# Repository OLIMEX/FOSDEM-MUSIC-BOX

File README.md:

# FOSDEM-MUSIC-BOX

Soldering kit programmable with Arduino IDE to play music

Product page: https://www.olimex.com/Products/Soldering-Kits/FOSDEM-MUSIC-BOX/open-source-hardware

## License
* Hardware is with CERN OHL v1.2 license
* Software is released under GPL3 License
* Documentation is released under CC BY-SA 3.0

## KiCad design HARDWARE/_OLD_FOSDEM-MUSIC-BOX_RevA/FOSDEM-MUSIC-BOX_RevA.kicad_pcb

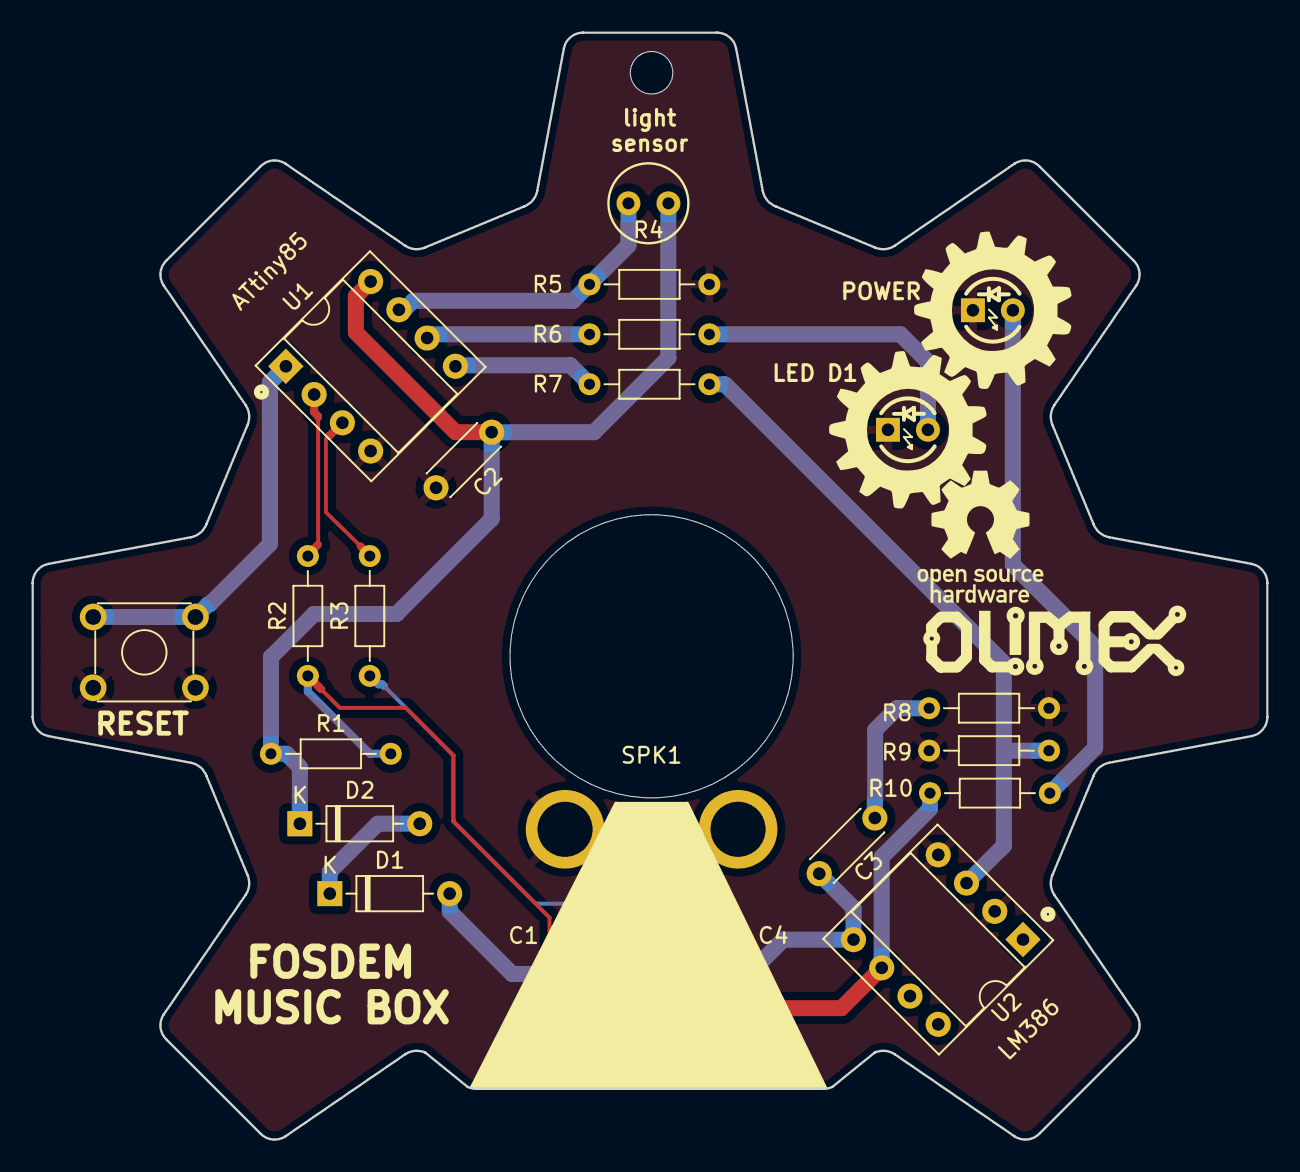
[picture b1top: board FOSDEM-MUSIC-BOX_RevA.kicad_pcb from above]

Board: 2 copper layers, 78.5 x 70.4 mm, 24 parts (0 on the bottom side), 18 nets.

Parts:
C1: 10uF; CP_Radial_D5.0mm_P2.00mm
C2: 100 nF; C_Disc_D4.3mm_W1.9mm_P5.00mm
C3: 100nF; C_Disc_D4.3mm_W1.9mm_P5.00mm
C4: 220uF_16V; CP_Radial_D6.3mm_P2.50mm
D1, D2: 1N4148; D_DO-35_SOD27_P7.62mm_Horizontal
LED1, LED2: LED_AK; LED-3mm-PTH-KA
MountingHole: NPTH_2.7mm
R1, R6, R7, R10: 1.5K; R_Axial_DIN0204_L3.6mm_D1.6mm_P7.62mm_Horizontal
R2, R3, R8: 22R; R_Axial_DIN0204_L3.6mm_D1.6mm_P7.62mm_Horizontal
R4: SNS-LDR5MM; R_PHOTO
R5, R9: 10K; R_Axial_DIN0204_L3.6mm_D1.6mm_P7.62mm_Horizontal
SPK1: 8R; SPEAKER_28mm
SW1: T1101GP(6x3x4.3MM); SW_TH_Tactile_Omron_B3F-10xx
U1: ATTINY85-20PU; DIP-8_W7.62mm_Socket
U2: LM386N; DIP-8_W7.62mm_Socket
USB1: USB_B; USB-B-EDGE

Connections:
GND: C1.2, C2.2, LED1.2, LED2.2, R5.2, R8.2, R9.1, SPK1.2, SW1.1, U1.4, U2.2, U2.4, USB1.0, USB1.4
unnamed: C1.1, D1.2, R10.1, U2.6, USB1.1
unnamed: C3.1, C4.1, U2.5
unnamed: C3.2, R8.1
unnamed: C4.2, SPK1.1
unnamed: C2.1, D2.1, R1.1, R4.1, U1.8
unnamed: D1.1, D2.2
unnamed: LED1.1, R6.2
unnamed: LED2.1, R10.2
unnamed: R1.2, R2.1, USB1.2
unnamed: R2.2, U1.2
unnamed: R3.1, USB1.3
unnamed: R3.2, U1.3
unnamed: R6.1, U1.6
unnamed: R4.2, R5.1, U1.7
unnamed: R7.1, R9.2, U2.3
unnamed: R7.2, U1.5
unnamed: SW1.2, U1.1

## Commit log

2020-01-16 initial upload hardware, software, licensee
2020-01-16 assembly docs
2020-02-04 Added BOM

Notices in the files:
HARDWARE/_OLD_FOSDEM-MUSIC-BOX_RevA/FOSDEM-MUSIC-BOX_RevA.kicad_pcb:
(c)2020
